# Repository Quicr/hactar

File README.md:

# Device updater

Static GitHub Pages updater written in plain JavaScript, using Web Serial. No
build step, WASM, CDN dependencies, or backend is needed.

## Usage

Open the site in desktop Chrome or Edge, connect the device over USB, select the
chips, and click **Update Device**. Select the device's USB serial port. Close
`ctl`, serial monitors, and other programs using that port first.

Choose a **Firmware version** to select the firmware set under `build/`. The
default is **main**. All chips in an update use the selected folder, and the
selection is locked until the update finishes.

The default update order is **MGMT → UI → NET**. Individual chips can also be
selected. UI and NET updates require MGMT firmware implementing the LINK protocol
from `~/code/link`. The update log is available under **Advanced Options**.

When flashing MGMT, choose **EV16 and older** or **EV17 and newer** (the default).
Every MGMT update applies the selected version: `16` or `17` in the STM32 DATA0
option byte, respectively. The updater preserves the other option bytes, updates
the DATA0 complement, and verifies the result before starting MGMT. If the value
and complement already match, the option-byte read verifies them without an
unnecessary rewrite. The version controls require MGMT to be selected; they
describe the hardware revision, not the firmware release.
Current MGMT firmware only starts when DATA0 is `16` or `17`, so select the
appropriate revision when configuring a chip with an unset board version.

MGMT automatically enters its ROM bootloader using the EV16 DTR/RTS reset
sequence. For boards without automatic reset, set MGMT BOOT0 high, reset the
device, and enable **MGMT is already in bootloader mode** before starting.
After a manual update, release BOOT0 and reset the device to boot normally.

If the browser's serial port rejects DTR/RTS control (`setSignals`), the updater
continues using serial data without automatic MGMT reset. UI and NET updates
still use MGMT's LINK commands to control their boot and reset pins. For MGMT,
enter its bootloader manually if it is not already active; the updater reports
the manual-reset steps if the bootloader does not respond.

Before talking to running MGMT firmware, the updater explicitly releases RTS
(BOOT0) and then DTR (reset), including after reopening the port to change baud
rate. Some serial drivers assert those lines when opening the port.

If MGMT does not answer, open **Advanced Options** for handshake retry details
and the number of serial bytes received. Verify that the selected port is the
device's port and that a manually asserted BOOT0 pin has been released. To
install a replacement `build/main/mgmt/mgmt.bin` on the device, select **MGMT** when
updating; UI/NET-only updates use the MGMT firmware already on the device.

## Firmware files

Publish these files alongside `index.html` for the default `main` firmware set:

| Chip | File | Flash address |
| --- | --- | --- |
| MGMT (STM32F072CB) | `build/main/mgmt/mgmt.bin` | `0x08000000` |
| UI (STM32F405RG) | `build/main/ui/ui.bin` | `0x08000000` |
| NET (ESP32-S3) | `build/main/net/bootloader.bin` | `0x0000` |
| NET | `build/main/net/partition-table.bin` | `0x8000` |
| NET | `build/main/net/net.bin` | `0x10000` |

Additional firmware sets use the same layout in another immediate subfolder,
for example `build/preview/mgmt/mgmt.bin`, `build/preview/ui/ui.bin`, and
`build/preview/net/...`.

The dropdown reads `build/manifest.json`, since GitHub Pages does not provide
directory listings. After adding or removing firmware folders, regenerate and
publish the manifest along with the binaries:

```sh
python3 scripts/generate-firmware-manifest.py
```

The script discovers immediate, non-hidden directories under `build/` and places
`main` first. Include this command in the firmware publishing job when automating
uploads. Missing files in a selected folder stop the update before opening the
serial port; the updater never substitutes binaries from another folder.

NET addresses follow the existing ESP-IDF build's `flasher_args.json`. Its app
must occupy the partition starting at `0x10000`; if the firmware layout changes,
update the addresses in `scripts/flasher.js` together with the binaries.
All selected images download before flashing starts. Only the required STM32
pages/sectors and NET image regions are erased. STM32 images are verified by
reading them back; NET images are checked using the ROM's MD5 command.

## Protocol

- MGMT ROM: 115200 baud, 8E1, STM32 AN3155 bootloader protocol.
- Running MGMT: 1000000 baud, 8E1, `LINK` frames with little-endian type/length.
- UI ROM: 115200 baud, 8E1 on the internal UART, tunneled with `ToUi`/`FromUi`.
- NET ROM: internal UART remains at 1000000 baud, 8N1, SLIP packets tunneled
  with `ToNet`/`FromNet`. Uses the ROM directly without uploading a stub.
- Only Hello, SetPin, SetUiBaudRate, and the two data tunnels are implemented.
  Reset timings and pin identifiers follow `link/src/ctl/{core,flash}.rs`.

The other chip is held in reset during UI/NET flashing and restored afterward.

## Local development

Serve the repository root, for example:

```sh
python3 -m http.server 8000
```

Open `http://localhost:8000`. Web Serial requires HTTPS or localhost; opening
`index.html` directly is not supported. GitHub Pages supplies HTTPS.

Protocol checks use Node's built-in test runner:

```sh
node --experimental-default-type=module --test tests/*.test.js
```

Actual USB flashing must also be checked with a physical device.

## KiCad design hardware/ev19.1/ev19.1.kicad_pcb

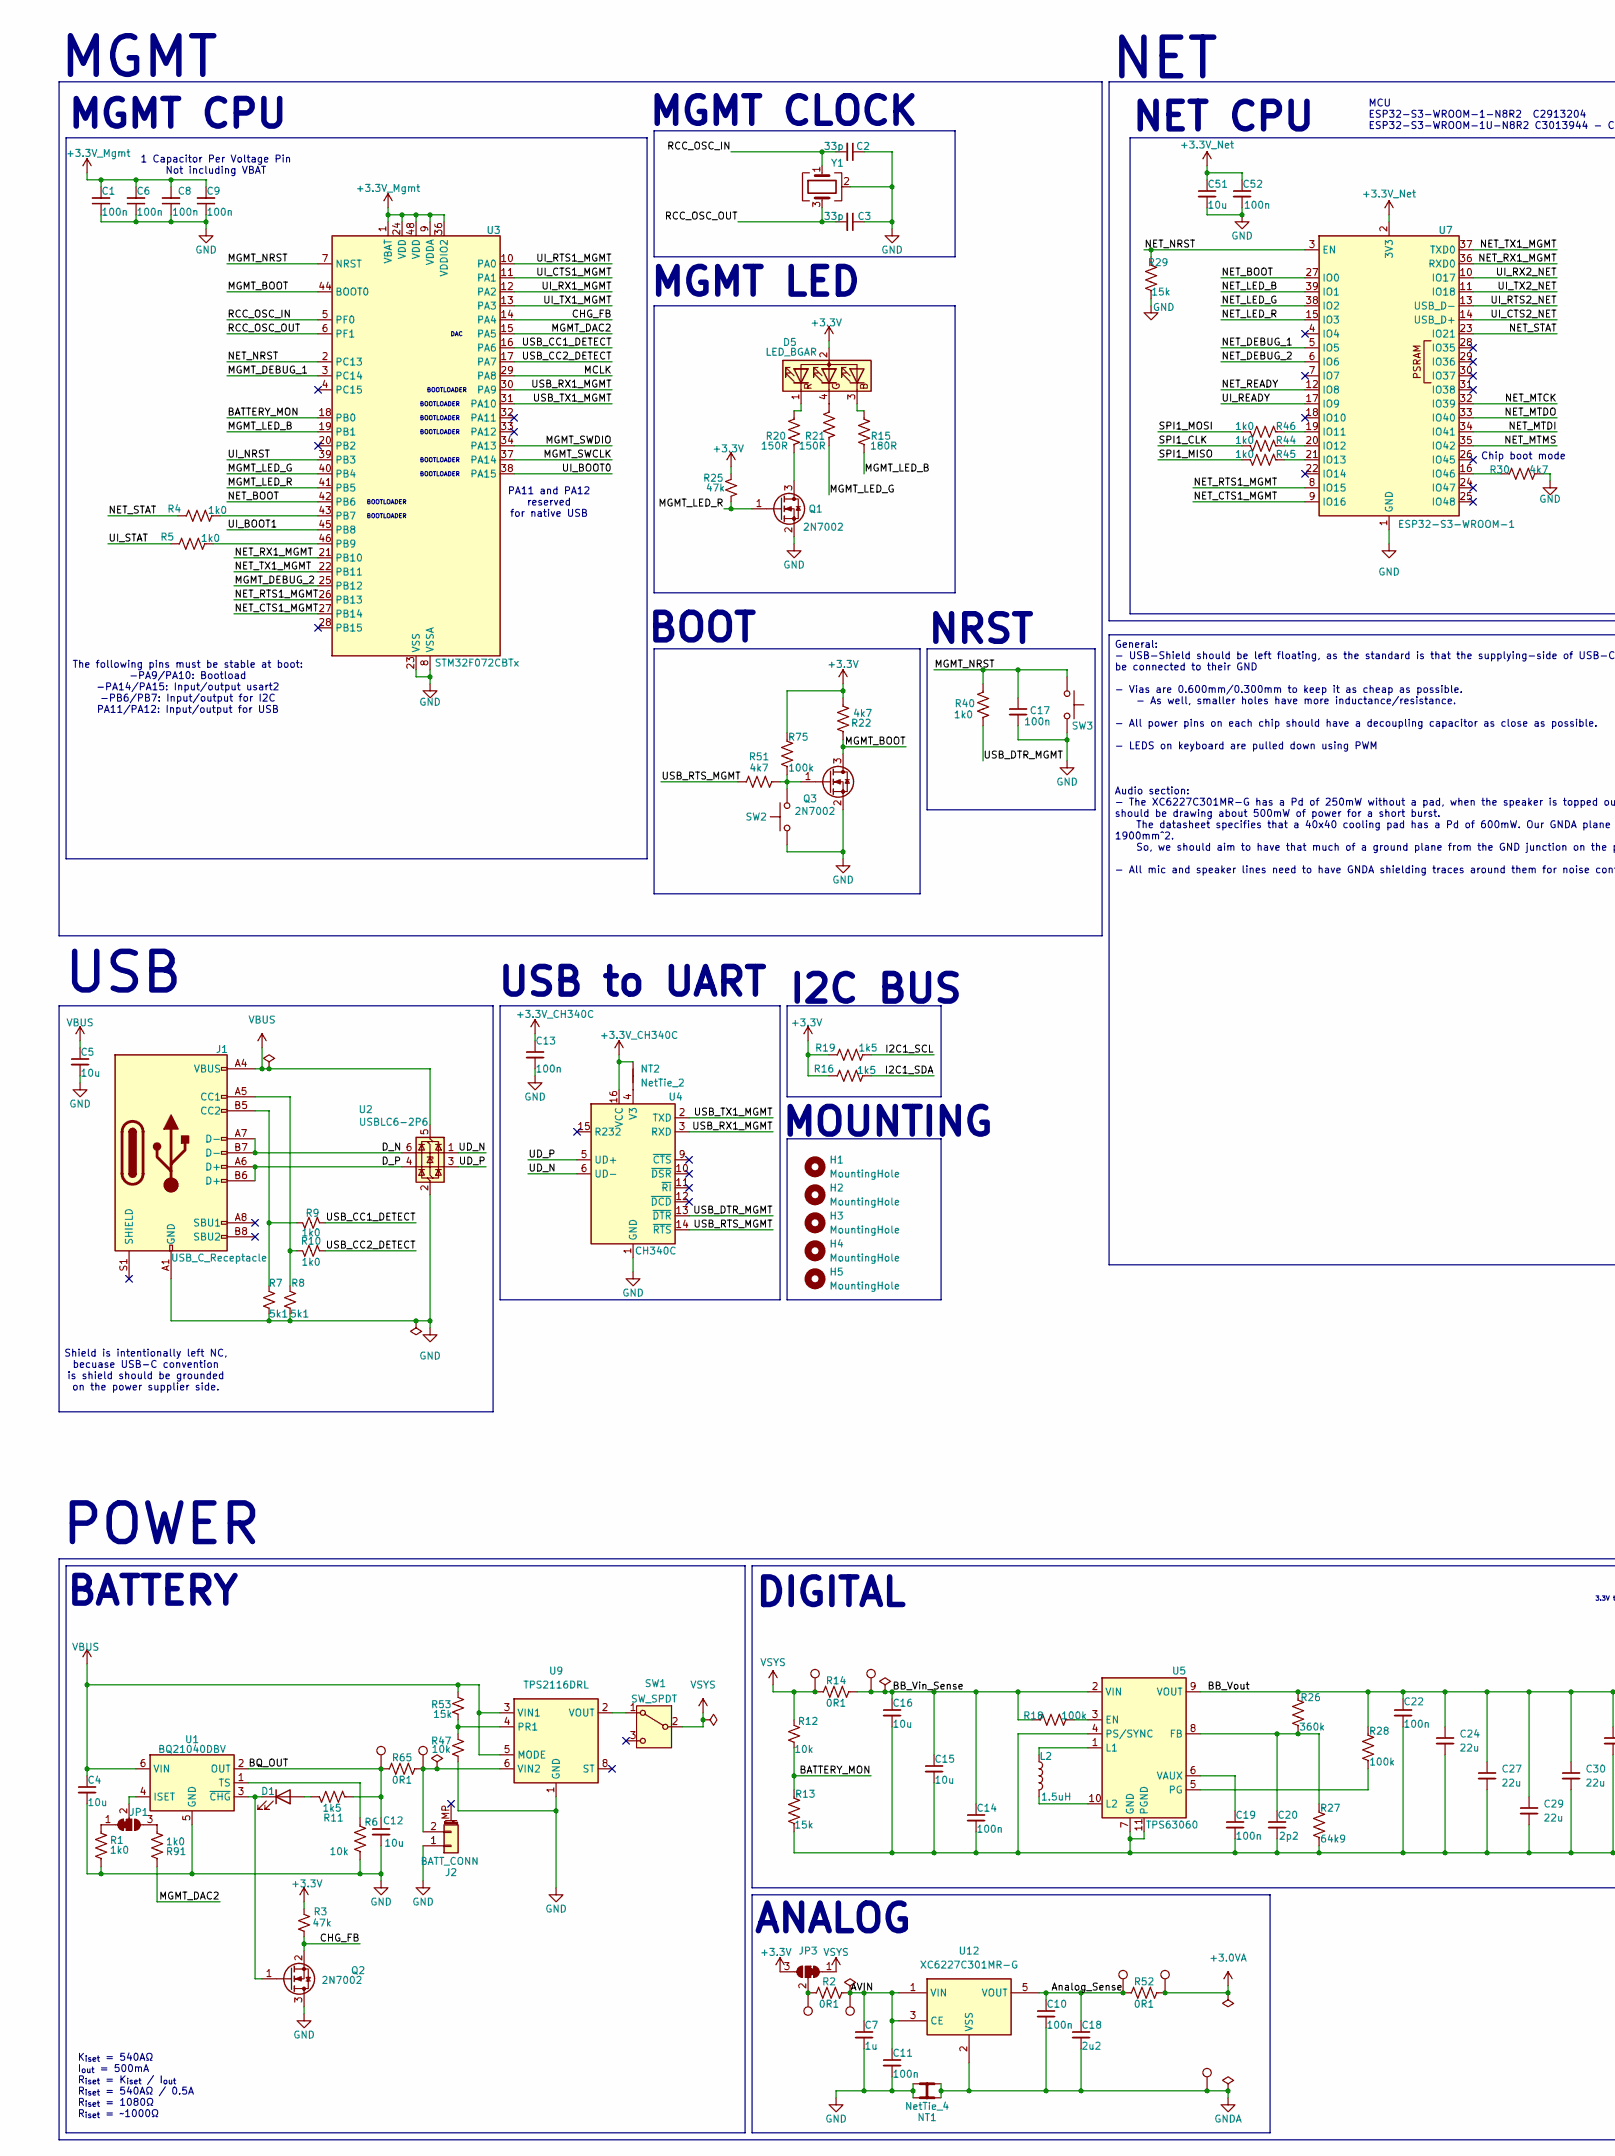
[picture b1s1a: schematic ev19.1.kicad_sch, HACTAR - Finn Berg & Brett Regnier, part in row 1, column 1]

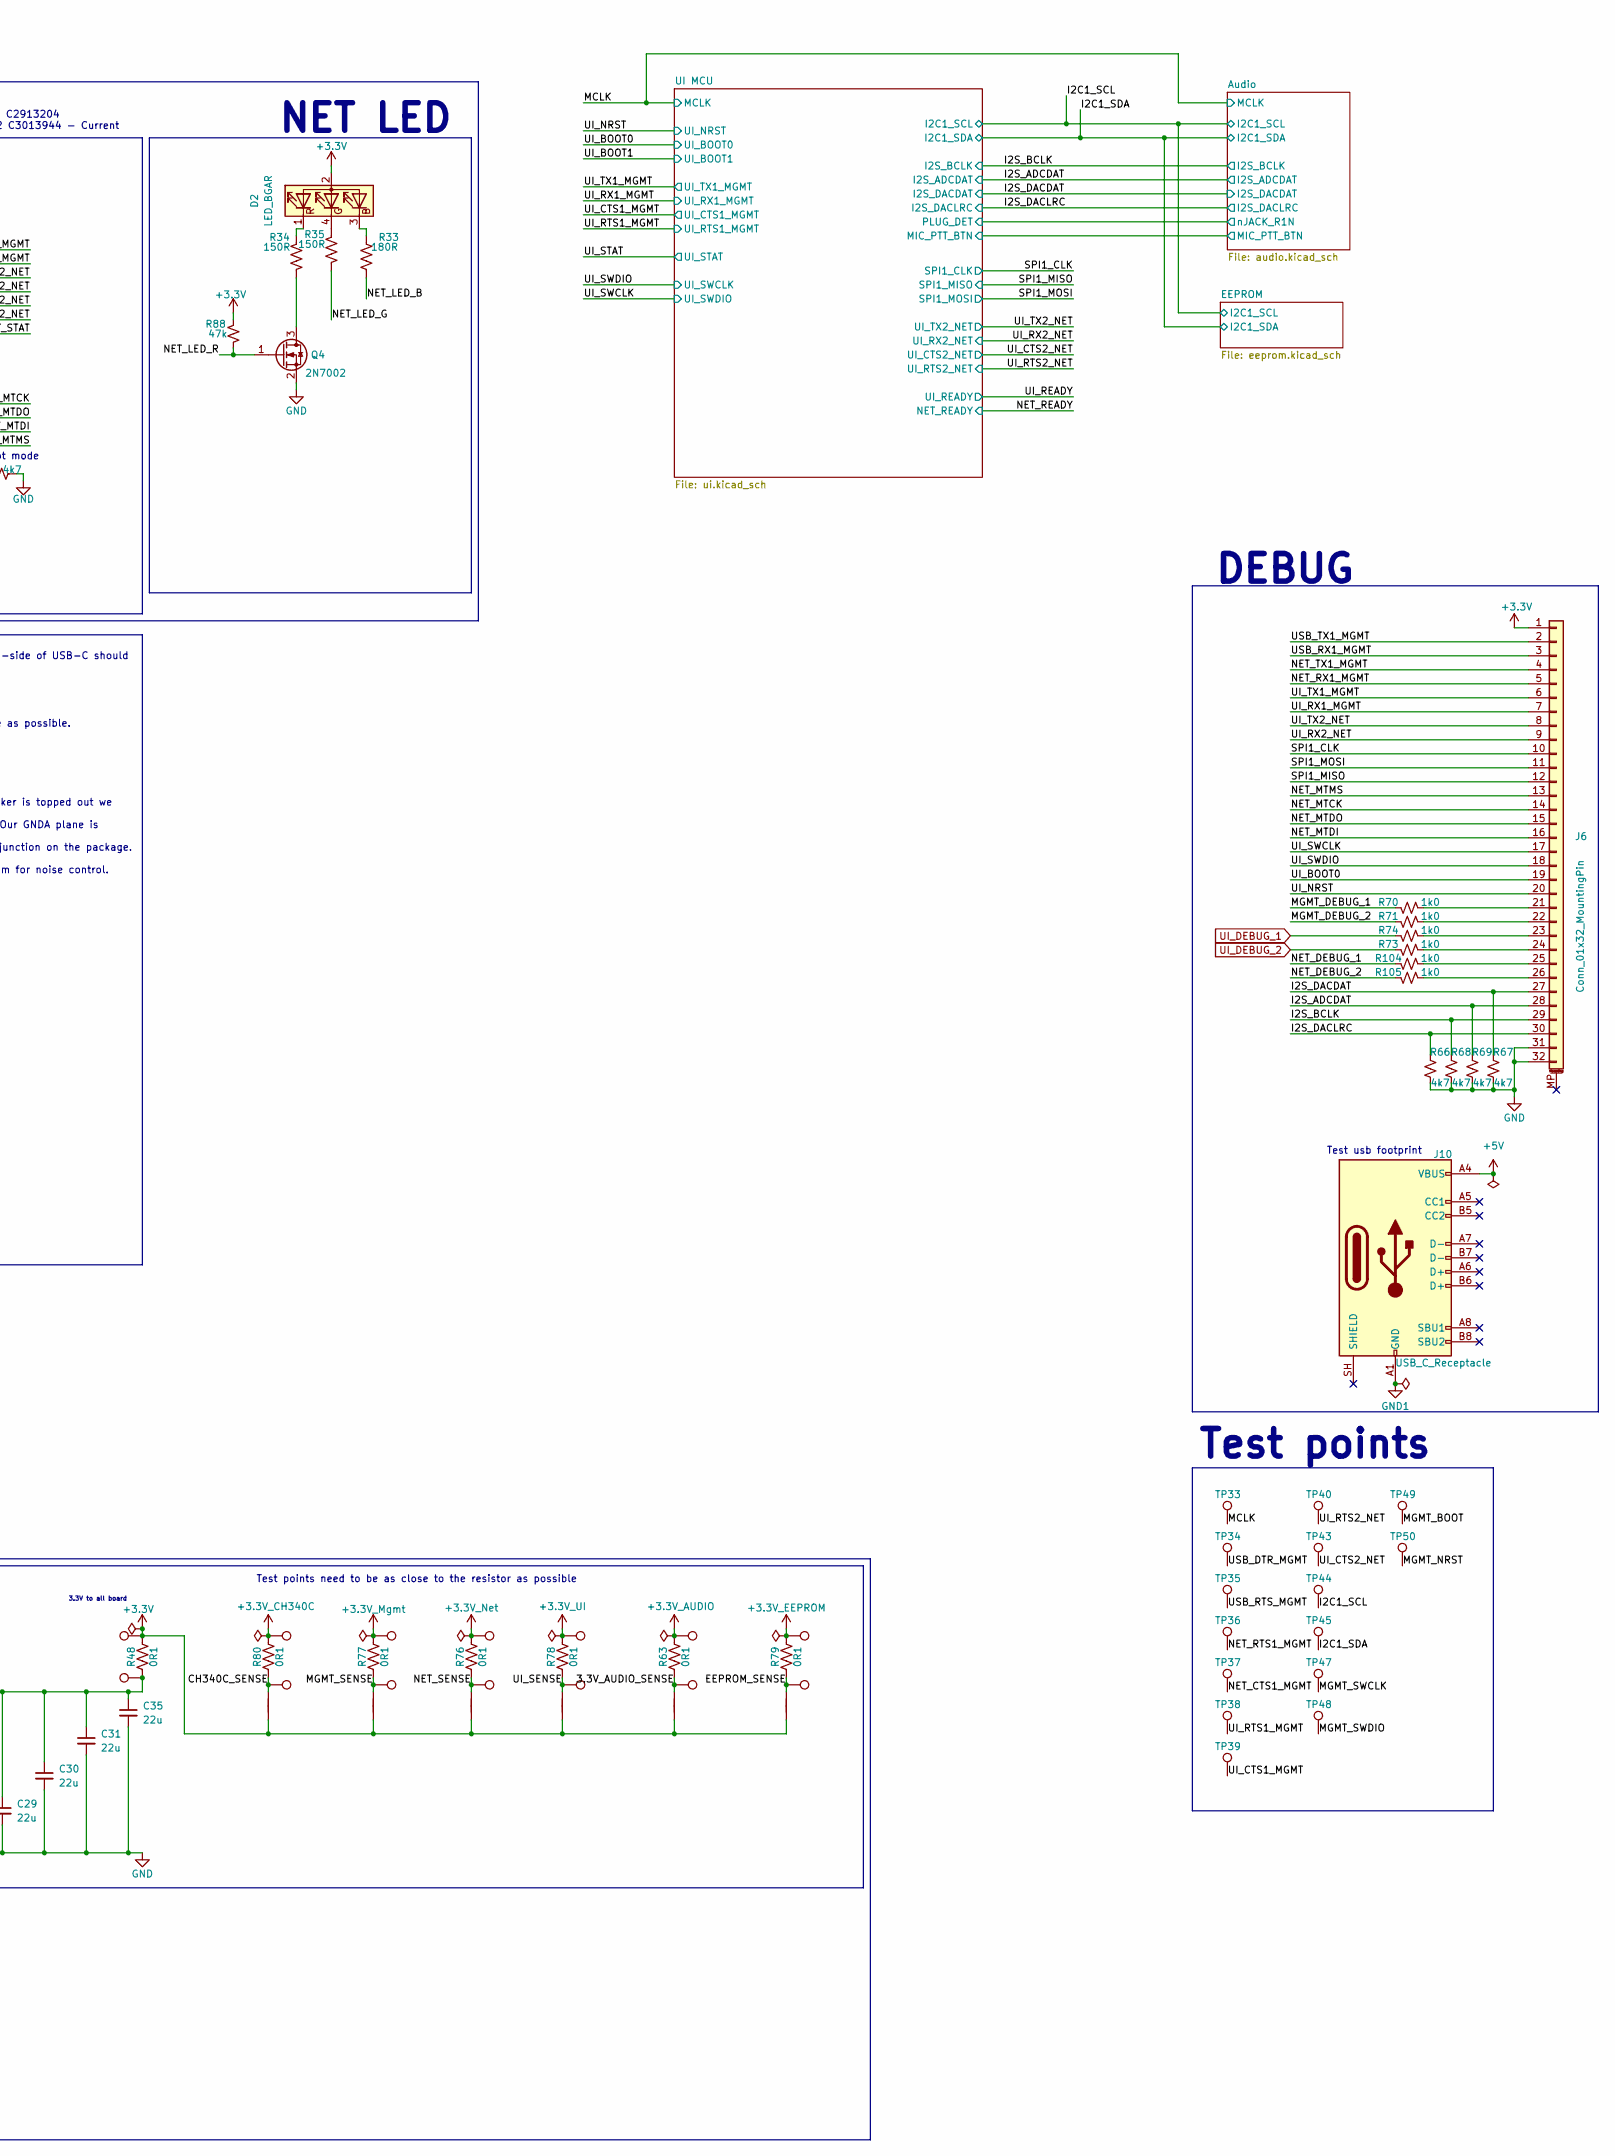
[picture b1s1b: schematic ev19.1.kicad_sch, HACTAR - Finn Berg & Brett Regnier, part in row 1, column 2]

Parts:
C1, C6, C8, C9, C13, C17, C52: 100n; C_0402_1005Metric; JLCPCB Part # C1525
C2, C3: 33p; C_0805_2012Metric; JLCPCB Part # C107115
C4, C5, C12: 10u; C_0402_1005Metric; JLCPCB Part # C307415
C7: 1u; C_0805_2012Metric; JLCPCB Part # C28323
C10, C11, C14, C19, C22: 100n; C_0805_2012Metric; JLCPCB Part # C85866
C15, C16, C51: 10u; C_0805_2012Metric; JLCPCB Part # C87157
C18: 2u2; C_0805_2012Metric; JLCPCB Part # C377773
C20: 2p2; C_0805_2012Metric; JLCPCB Part # C519933
C24, C27, C29, C30, C31, C35: 22u; C_0805_2012Metric; JLCPCB Part # C5674
D1: LED; D_0805_2012Metric; JLCPCB Part # C130114
D2, D5: LED_BGAR; LED-ARRAY-SMD_4P-L1.6-W1.5-TL_NH-B1515RGBA; JLCPCB Part # C2874115
H1, H2, H3, H4: MountingHole; MountingHole_2.7mm_M2.5
H5: MountingHole; Standoff_Hole
J1: USB_C_Receptacle; USB-C_SMD-TYPE-C-31-M-12; JLCPCB Part # C165948
J2: BATT_CONN; JST_PH_S2B-PH-SM4-TB_1x02-1MP_P2.00mm_Horizontal; JLCPCB Part # C295747
J6: Conn_01x32_MountingPin; Hirose_FH12-32S-0.5SH_1x32-1MP_P0.50mm_Horizontal; JLCPCB Part # C597985
J10: USB_C_Receptacle; USB_C_Receptacle_HRO_TYPE-C-31-M-12; JLCPCB Part # C165948
JP1: SolderJumper_3_Bridged12
JP3: SolderJumper_3_Bridged12; SolderJumper-3_P1.3mm_Bridged12_RoundedPad1.0x1.5mm
L2: 1.5uH; L_Coilcraft_XxL4020; JLCPCB Part # C3033018
NT1: NetTie_4; NetTie-4_SMD_Pad0.5mm
NT2, NT5, NT6, NT7, NT8, NT9, NT10: NetTie_2; NetTie-2_SMD_Pad0.5mm
Q1, Q2, Q3, Q4: 2N7002; SOT-23; JLCPCB Part # C8545
R1, R4, R5, R9, R10, R40, R44, R45, R46, R70, R71, R73, R74, R91, R104, R105: 1k0; R_0402_1005Metric; JLCPCB Part # C11702
R2, R14, R48, R52, R63, R65, R76, R77, R78, R79, R80: 0R1; R_1206_3216Metric; JLCPCB Part # C25334
R3, R25, R88: 47k; R_0402_1005Metric; JLCPCB Part # C25792
R6, R12, R47: 10k; R_0402_1005Metric; JLCPCB Part # C25744
R7, R8: 5k1; R_0402_1005Metric; JLCPCB Part # C25905
R11, R16, R19: 1k5; R_0402_1005Metric; JLCPCB Part # C25867
R13, R29, R53: 15k; R_0402_1005Metric; JLCPCB Part # C25756
R15, R33: 180R; R_0402_1005Metric; JLCPCB Part # C25087
R18, R28, R75: 100k; R_0402_1005Metric; JLCPCB Part # C25741
R20, R21, R34, R35: 150R; R_0402_1005Metric; JLCPCB Part # C25082
R22, R30, R51, R66, R67, R68, R69: 4k7; R_0402_1005Metric; JLCPCB Part # C25900
R26: 360k; R_0402_1005Metric; JLCPCB Part # C45956
R27: 64k9; R_0402_1005Metric; JLCPCB Part # C26984
SW1: SW_SPDT; SW-SMD_MK-12C02-G020; JLCPCB Part # C963206
SW2, SW3: SW_Push; KEY-SMD_4P-L4.2-W3.2-P2.20-LS4.6; JLCPCB Part # C139797
TP8: TestPoint; TestPoint_THTPad_D2.0mm_Drill1.0mm
TP11, TP12, TP13, TP14, TP15, TP16, TP17, TP18, TP19, TP20, TP21, TP22, TP23, TP24, TP25, TP26, TP27, TP28, TP29, TP30, TP31, TP32, TP33, TP34, TP35, TP36, TP37, TP38, TP39, TP40, TP43, TP44, TP45, TP47, TP48, TP49, TP50: TestPoint; TestPoint_Pad_D2.0mm
U1: BQ21040DBV; SOT-23-6; JLCPCB Part # C202311
U2: USBLC6-2P6; SOT-666; JLCPCB Part # C2827693
U3: STM32F072CBTx; LQFP-48_7x7mm_P0.5mm; JLCPCB Part # C80488
U4: CH340C; SOIC-16_3.9x9.9mm_P1.27mm; JLCPCB Part # C7464026
U5: TPS63060; Texas_S-PWSON-N10_ThermalVias; JLCPCB Part # C48567
U7: ESP32-S3-WROOM-1; JLCPCB Part # C2913204
U9: TPS2116DRL; SOT-583-8; JLCPCB Part # C3235557
U12: XC6227C301MR-G; SOT-23-5; JLCPCB Part # C484285
Y1: Crystal_GND24; Crystal_SMD_3225-4Pin_3.2x2.5mm; JLCPCB Part # C13738

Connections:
+3.0VA: R52.2, TP28.1 (1_1); also elsewhere on the board
+3.3V: D2.2 (A), D5.2 (A), J6.1, JP3.3 (B), NT5.1, NT6.1, NT7.1, NT8.1, NT9.1, NT10.1, R3.2, R16.1, R19.1, R22.2, R25.2, R48.2, R75.2, R88.2, TP24.1 (1_1); also elsewhere on the board
+3.3V_AUDIO: R63.2, TP13.1 (1_1); also elsewhere on the board
+3.3V_CH340C: C13.1, NT2.2, R80.2, TP21.1 (1_1), U4.16 (VCC)
+3.3V_EEPROM: R79.2, TP12.1 (1_1); also elsewhere on the board
+3.3V_Mgmt: C1.2, C6.2, C8.2, C9.2, R77.2, TP19.1 (1_1), U3.1 (VBAT), U3.9 (VDDA), U3.24 (VDD), U3.36 (VDDIO2), U3.48 (VDD)
+3.3V_Net: C51.1, C52.1, R76.2, TP17.1 (1_1), U7.2 (3V3)
+3.3V_UI: R78.2, TP15.1 (1_1); also elsewhere on the board
/3.3V_AUDIO_SENSE: NT9.2, R63.1, TP14.1 (1_1)
/AVIN: C7.1, C11.1, R2.2, TP30.1 (1_1), U12.1 (VIN), U12.3 (CE)
/Analog_Sense: C10.1, C18.1, R52.1, TP27.1 (1_1), U12.5 (VOUT)
/BATTERY_MON: R12.1, R13.1, U3.18 (PB0)
/BB_Vin_Sense: C14.1, C15.1, C16.1, R14.2, R18.1, TP26.1 (1_1), U5.2 (VIN)
/BB_Vout: C22.1, C24.1, C27.1, C29.1, C30.1, C31.1, C35.1, R26.2, R28.2, R48.1, TP23.1 (1_1), U5.9 (VOUT)
/BQ_OUT: C12.1, R11.1, R65.1, TP31.1 (1_1), U1.2 (OUT)
/CH340C_SENSE: NT5.2, R80.1, TP22.1 (1_1)
/CHG_FB: Q2.2 (S), R3.1, U3.14 (PA4)
/D_N: J1.A7 (D-), J1.B7 (D-), U2.6 (I/O1)
/D_P: J1.A6 (D+), J1.B6 (D+), U2.4 (I/O2)
/EEPROM_SENSE: NT10.2, R79.1, TP11.1 (1_1)
/I2C1_SCL: R19.2, TP44.1 (1_1); also elsewhere on the board
/I2C1_SDA: R16.2, TP45.1 (1_1); also elsewhere on the board
/I2S_ADCDAT: J6.28, R69.1; also elsewhere on the board
/I2S_BCLK: J6.29, R68.1; also elsewhere on the board
/I2S_DACDAT: J6.27, R67.1; also elsewhere on the board
/I2S_DACLRC: J6.30, R66.1; also elsewhere on the board
/MCLK: TP33.1 (1_1), U3.29 (PA8); also elsewhere on the board
/MGMT_BOOT: Q3.3 (D), R22.1, TP49.1 (1_1), U3.44 (BOOT0)
/MGMT_DAC2: R91.1, U3.15 (PA5)
/MGMT_DEBUG_1: R70.1, U3.3 (PC14)
/MGMT_DEBUG_2: R71.1, U3.25 (PB12)
/MGMT_LED_B: R15.2, U3.19 (PB1)
/MGMT_LED_G: R21.2, U3.40 (PB4)
/MGMT_LED_R: Q1.1 (G), R25.1, U3.41 (PB5)
/MGMT_NRST: C17.1, R40.1, SW3.3, SW3.4, TP50.1 (1_1), U3.7 (NRST)
/MGMT_SENSE: NT6.2, R77.1, TP20.1 (1_1)
/MGMT_SWCLK: TP47.1 (1_1), U3.37 (PA14)
/MGMT_SWDIO: TP48.1 (1_1), U3.34 (PA13)
/NET_BOOT: U3.42 (PB6), U7.27 (IO0)
/NET_CTS1_MGMT: TP37.1 (1_1), U3.27 (PB14), U7.9 (IO16)
/NET_DEBUG_1: R104.2, U7.5 (IO5)
/NET_DEBUG_2: R105.2, U7.6 (IO6)
/NET_LED_B: R33.1, U7.39 (IO1)
/NET_LED_G: R35.1, U7.38 (IO2)
/NET_LED_R: Q4.1 (G), R88.1, U7.15 (IO3)
/NET_MTCK: J6.14, U7.32 (IO39)
/NET_MTDI: J6.16, U7.34 (IO41)
/NET_MTDO: J6.15, U7.33 (IO40)
/NET_MTMS: J6.13, U7.35 (IO42)
/NET_NRST: R29.1, U3.2 (PC13), U7.3 (EN)
/NET_READY: U7.12 (IO8); also elsewhere on the board
/NET_RTS1_MGMT: TP36.1 (1_1), U3.26 (PB13), U7.8 (IO15)
/NET_RX1_MGMT: J6.5, U3.21 (PB10), U7.36 (RXD0)
/NET_SENSE: NT7.2, R76.1, TP18.1 (1_1)
/NET_STAT: R4.2, U7.23 (IO21)
/NET_TX1_MGMT: J6.4, U3.22 (PB11), U7.37 (TXD0)
/RCC_OSC_IN: C2.2, U3.5 (PF0), Y1.1
/RCC_OSC_OUT: C3.2, U3.6 (PF1), Y1.3
/SPI1_CLK: J6.10, R44.1; also elsewhere on the board
/SPI1_MISO: J6.12, R45.1; also elsewhere on the board
/SPI1_MOSI: J6.11, R46.1; also elsewhere on the board
/UD_N: U2.1 (I/O1), U4.6 (UD-)
/UD_P: U2.3 (I/O2), U4.5 (UD+)
/UI_BOOT0: J6.19, U3.38 (PA15); also elsewhere on the board
/UI_BOOT1: U3.45 (PB8); also elsewhere on the board
/UI_CTS1_MGMT: TP39.1 (1_1), U3.11 (PA1); also elsewhere on the board
/UI_CTS2_NET: TP43.1 (1_1), U7.14 (USB_D+); also elsewhere on the board
/UI_NRST: J6.20, U3.39 (PB3); also elsewhere on the board
/UI_READY: U7.17 (IO9); also elsewhere on the board
/UI_RTS1_MGMT: TP38.1 (1_1), U3.10 (PA0); also elsewhere on the board
/UI_RTS2_NET: TP40.1 (1_1), U7.13 (USB_D-); also elsewhere on the board
/UI_RX1_MGMT: J6.7, U3.12 (PA2); also elsewhere on the board
/UI_RX2_NET: J6.9, U7.10 (IO17); also elsewhere on the board
/UI_SENSE: NT8.2, R78.1, TP16.1 (1_1)
/UI_STAT: R5.2; also elsewhere on the board
/UI_SWCLK: J6.17; also elsewhere on the board
/UI_SWDIO: J6.18; also elsewhere on the board
/UI_TX1_MGMT: J6.6, U3.13 (PA3); also elsewhere on the board
/UI_TX2_NET: J6.8, U7.11 (IO18); also elsewhere on the board
/USB_CC1_DETECT: R9.1, U3.16 (PA6)
/USB_CC2_DETECT: R10.1, U3.17 (PA7)
/USB_DTR_MGMT: R40.2, TP34.1 (1_1), U4.13 (~DTR)
/USB_RTS_MGMT: R51.1, TP35.1 (1_1), U4.14 (~RTS)
/USB_RX1_MGMT: J6.3, U3.30 (PA9), U4.3 (RXD)
/USB_TX1_MGMT: J6.2, U3.31 (PA10), U4.2 (TXD)
GND: C1.1, C2.1, C3.1, C4.2, C5.2, C6.1, C7.2, C8.1, C9.1, C11.2, C12.2, C13.2, C14.2, C15.2, C16.2, C17.2, C19.2, C20.2, C22.2, C24.2, C27.2, C29.2, C30.2, C31.2, C35.2, C51.2, C52.2, J1.A1 (GND), J1.A12 (GND), J1.B1 (GND), J1.B12 (GND), J2.1, J6.31, J6.32, NT1.1, NT1.3, Q1.2 (S), Q2.3 (D), Q3.2 (S), Q4.2 (S), R1.2, R6.2, R7.1, R8.1, R13.2, R27.1, R29.2, R30.2, R47.1, R66.2, R67.2, R68.2, R69.2, SW2.1, SW2.2, SW3.1, SW3.2, U1.5 (GND), U2.2 (GND), U3.8 (VSSA), U3.23 (VSS), U3.35 (VSS), U3.47 (VSS), U4.1 (GND), U5.4 (PS/SYNC), U5.7 (GND), U5.11 (PGND), U7.1 (GND), U7.40 (GND), U7.41 (GND), U9.1 (GND), Y1.2 (G), Y1.4 (G); also elsewhere on the board
GNDA: C10.2, C18.2, NT1.2, NT1.4, TP8.1 (1_1), U12.2 (VSS); also elsewhere on the board
unnamed: D1.2 (A), R11.2
unnamed: D1.1 (K), Q2.1 (G), U1.3 (~CHG)
unnamed: D2.3 (BK), R33.2
unnamed: D2.4 (GK), R35.2
unnamed: D2.1 (RK), R34.2
unnamed: D5.3 (BK), R15.1
unnamed: D5.4 (GK), R21.1
unnamed: D5.1 (RK), R20.1
unnamed: J1.A5 (CC1), R8.2, R10.2
unnamed: J1.B5 (CC2), R7.2, R9.2
unnamed: J2.2, R65.2, TP32.1 (1_1), U9.6 (VIN2)
unnamed: J6.21, R70.2
unnamed: J6.22, R71.2
unnamed: J6.23, R74.1
unnamed: J6.24, R73.1
unnamed: J6.25, R104.1
unnamed: J6.26, R105.1
unnamed: J10.A1 (GND), J10.A12 (GND), J10.B1 (GND), J10.B12 (GND)
unnamed: J10.A4 (VBUS), J10.A9 (VBUS), J10.B4 (VBUS), J10.B9 (VBUS)
unnamed: JP1.1 (A), R1.1
unnamed: JP1.3 (B), R91.2
unnamed: JP1.2 (C), U1.4 (ISET)
unnamed: JP3.2 (C), R2.1, TP29.1 (1_1)
unnamed: Q1.3 (D), R20.2
unnamed: Q3.1 (G), R51.2, R75.1, SW2.3, SW2.4
unnamed: Q4.3 (D), R34.1
unnamed: SW1.1 (A), U9.2 (VOUT), U9.7 (VOUT)
unnamed: R6.1, U1.1 (TS)
unnamed: R4.1, U3.43 (PB7)
unnamed: R5.1, U3.46 (PB9)
unnamed: NT2.1, U4.4 (V3)
unnamed: R18.2, U5.3 (EN)
unnamed: C20.1, R26.1, R27.2, U5.8 (FB)
unnamed: L2.1, U5.1 (L1)
unnamed: L2.2, U5.10 (L2)
unnamed: R28.1, U5.5 (PG)
unnamed: C19.1, U5.6 (VAUX)
unnamed: R46.2, U7.19 (IO11)
unnamed: R44.2, U7.20 (IO12)
unnamed: R45.2, U7.21 (IO13)
unnamed: R30.1, U7.16 (IO46)
unnamed: R47.2, R53.1, U9.4 (PR1)
UI_DEBUG_1: R74.2; also elsewhere on the board
UI_DEBUG_2: R73.2; also elsewhere on the board
VBUS: C4.1, C5.1, J1.A4 (VBUS), J1.A9 (VBUS), J1.B4 (VBUS), J1.B9 (VBUS), R53.2, U1.6 (VIN), U2.5 (VBUS), U9.3 (VIN1), U9.5 (MODE)
VSYS: JP3.1 (A), R12.2, R14.1, SW1.2 (B), TP25.1 (1_1)

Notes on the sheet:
MGMT
BOOTLOADER
USB to UART
DAC
NET CPU
MGMT CLOCK
MGMT CPU
Test points need to be as close to the resistor as possible
NET
Test points
POWER
K_{iset} = 540AΩ I_{out} = 500mA R_{iset} = K_{iset} / I_{out} R_{iset} = 540AΩ / 0.5A R_{iset} = 1080Ω R_{iset} = ~1000Ω
MOUNTING
BATTERY
NET LED
Chip boot mode
NRST
The following pins must be stable at boot: -PA9/PA10: Bootload -PA14/PA15: Input/output usart2 -PB6/PB7: Input/output for I2C PA11/PA12: Input/output for USB
DIGITAL
Test usb footprint
Shield is intentionally left NC, becuase USB-C convention is shield should be grounded on the power supplier side.
MCU ESP32-S3-WROOM-1-N8R2 C2913204 ESP32-S3-WROOM-1U-N8R2 C3013944 - Current
BOOT
PA11 and PA12 reserved for native USB
I2C BUS
USB
MGMT LED
3.3V to all board
DEBUG
1 Capacitor Per Voltage Pin Not including VBAT
ANALOG
General: - USB-Shield should be left floating, as the standard is that the supplying-side of USB-C should be connected to their GND - Vias are 0.600mm/0.300mm to keep it as cheap as possible. - As well, smaller holes have more inductance/resistance. - All power pins on each chip should have a decou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

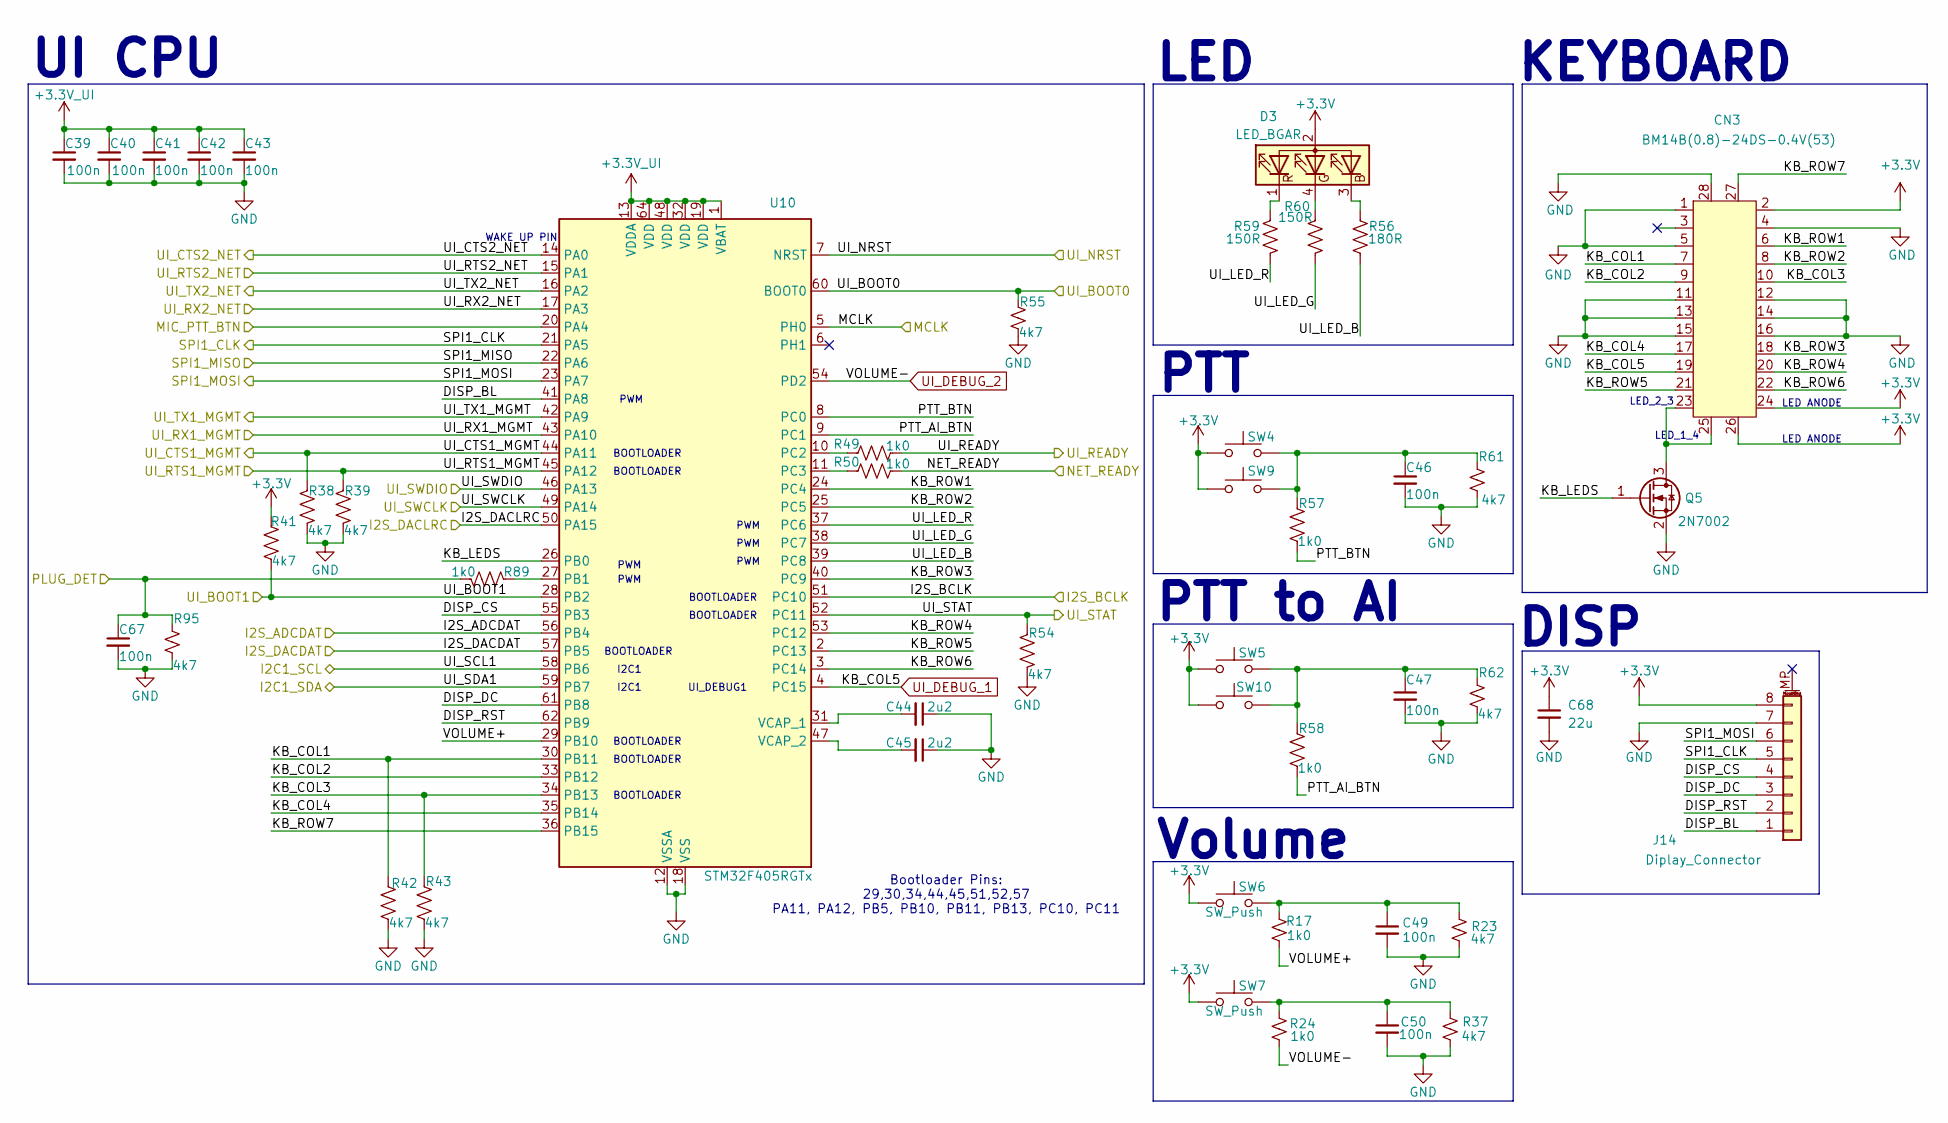
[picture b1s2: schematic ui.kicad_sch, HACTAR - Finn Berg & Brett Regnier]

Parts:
C39, C40, C41, C42, C43, C46, C47, C49, C50, C67: 100n; C_0402_1005Metric; JLCPCB Part # C1525
C44, C45: 2u2; C_0402_1005Metric; JLCPCB Part # C12530
C68: 22u; C_0805_2012Metric; JLCPCB Part # C5674
CN3: BM14B(0.8)-24DS-0.4V(53); BM14B(0.B)-24DS-0.4V(53); JLCPCB Part # C3640874
D3: LED_BGAR; LED-ARRAY-SMD_4P-L1.6-W1.5-TL_NH-B1515RGBA; JLCPCB Part # C2874115
J14: Diplay_Connector; JST_PH_S8B-PH-SM4-TB_1x08-1MP_P2.00mm_Horizontal; JLCPCB Part # C265121
Q5: 2N7002; SOT-23; JLCPCB Part # C8545
R17, R24, R49, R50, R57, R58, R89: 1k0; R_0402_1005Metric; JLCPCB Part # C11702
R23, R37, R38, R39, R41, R42, R43, R54, R55, R61, R62, R95: 4k7; R_0402_1005Metric; JLCPCB Part # C25900
R56: 180R; R_0402_1005Metric; JLCPCB Part # C25087
R59, R60: 150R; R_0402_1005Metric; JLCPCB Part # C25082
SW4, SW5, SW6, SW7: SW_Push; SW-SMD_SHOU_TS36CA-0.6; JLCPCB Part # C2906288
SW9, SW10: SW_Push; SW-SMD_4P-L5.1-W5.1-P3.70-LS6.5-TL_H1.5; JLCPCB Part # C318886
U10: STM32F405RGTx; LQFP-64_10x10mm_P0.5mm; JLCPCB Part # C15742

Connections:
+3.3V: C68.1, CN3.2, CN3.24, CN3.26, D3.2 (A), J14.8, R41.1, SW4.1, SW5.1, SW6.1, SW7.1, SW9.1, SW9.2, SW10.1, SW10.2; also elsewhere on the board
+3.3V_UI: C39.1, C40.1, C41.1, C42.1, C43.1, U10.1 (VBAT), U10.13 (VDDA), U10.19 (VDD), U10.32 (VDD), U10.48 (VDD), U10.64 (VDD); also elsewhere on the board
/Audio/MIC_PTT_BTN: U10.20 (PA4); also elsewhere on the board
/Audio/nJACK_R1N: C67.1, R89.1, R95.2; also elsewhere on the board
/I2C1_SCL: U10.58 (PB6); also elsewhere on the board
/I2C1_SDA: U10.59 (PB7); also elsewhere on the board
/I2S_ADCDAT: U10.56 (PB4); also elsewhere on the board
/I2S_BCLK: U10.51 (PC10); also elsewhere on the board
/I2S_DACDAT: U10.57 (PB5); also elsewhere on the board
/I2S_DACLRC: U10.50 (PA15); also elsewhere on the board
/MCLK: U10.5 (PH0); also elsewhere on the board
/NET_READY: R50.1; also elsewhere on the board
/SPI1_CLK: J14.5, U10.21 (PA5); also elsewhere on the board
/SPI1_MISO: U10.22 (PA6); also elsewhere on the board
/SPI1_MOSI: J14.6, U10.23 (PA7); also elsewhere on the board
/UI MCU/DISP_BL: J14.1, U10.41 (PA8)
/UI MCU/DISP_CS: J14.4, U10.55 (PB3)
/UI MCU/DISP_DC: J14.3, U10.61 (PB8)
/UI MCU/DISP_RST: J14.2, U10.62 (PB9)
/UI MCU/KB_COL1: CN3.7, R42.2, U10.30 (PB11)
/UI MCU/KB_COL2: CN3.9, U10.33 (PB12)
/UI MCU/KB_COL3: CN3.10, R43.2, U10.34 (PB13)
/UI MCU/KB_COL4: CN3.17, U10.35 (PB14)
/UI MCU/KB_LEDS: Q5.1 (G), U10.26 (PB0)
/UI MCU/KB_ROW1: CN3.6, U10.24 (PC4)
/UI MCU/KB_ROW2: CN3.8, U10.25 (PC5)
/UI MCU/KB_ROW3: CN3.18, U10.40 (PC9)
/UI MCU/KB_ROW4: CN3.20, U10.53 (PC12)
/UI MCU/KB_ROW5: CN3.21, U10.2 (PC13)
/UI MCU/KB_ROW6: CN3.22, U10.3 (PC14)
/UI MCU/KB_ROW7: CN3.27, U10.36 (PB15)
/UI MCU/PTT_AI_BTN: R58.1, U10.9 (PC1)
/UI MCU/PTT_BTN: R57.1, U10.8 (PC0)
/UI MCU/UI_LED_B: R56.1, U10.39 (PC8)
/UI MCU/UI_LED_G: R60.1, U10.38 (PC7)
/UI MCU/UI_LED_R: R59.1, U10.37 (PC6)
/UI MCU/VOLUME+: R17.1, U10.29 (PB10)
/UI_BOOT0: R55.1, U10.60 (BOOT0); also elsewhere on the board
/UI_BOOT1: R41.2, U10.28 (PB2); also elsewhere on the board
/UI_CTS1_MGMT: R38.2, U10.44 (PA11); also elsewhere on the board
/UI_CTS2_NET: U10.14 (PA0); also elsewhere on the board
/UI_NRST: U10.7 (NRST); also elsewhere on the board
/UI_READY: R49.1; also elsewhere on the board
/UI_RTS1_MGMT: R39.2, U10.45 (PA12); also elsewhere on the board
/UI_RTS2_NET: U10.15 (PA1); also elsewhere on the board
/UI_RX1_MGMT: U10.43 (PA10); also elsewhere on the board
/UI_RX2_NET: U10.17 (PA3); also elsewhere on the board
/UI_STAT: R54.2, U10.52 (PC11); also elsewhere on the board
/UI_SWCLK: U10.46 (PA13); also elsewhere on the board
/UI_SWDIO: U10.49 (PA14); also elsewhere on the board
/UI_TX1_MGMT: U10.42 (PA9); also elsewhere on the board
/UI_TX2_NET: U10.16 (PA2); also elsewhere on the board
GND: C39.2, C40.2, C41.2, C42.2, C43.2, C44.1, C45.1, C46.2, C47.2, C49.2, C50.2, C67.2, C68.2, CN3.1, CN3.4, CN3.5, CN3.11, CN3.12, CN3.13, CN3.14, CN3.15, CN3.16, CN3.28, J14.7, Q5.2 (S), R23.1, R37.1, R38.1, R39.1, R42.1, R43.1, R54.1, R55.2, R61.1, R62.1, R95.1, U10.12 (VSSA), U10.18 (VSS), U10.63 (VSS); also elsewhere on the board
unnamed: C46.1, R57.2, R61.2, SW4.2, SW9.3, SW9.4
unnamed: C47.1, R58.2, R62.2, SW5.2, SW10.3, SW10.4
unnamed: C49.1, R17.2, R23.2, SW6.2
unnamed: C50.1, R24.2, R37.2, SW7.2
unnamed: D3.3 (BK), R56.2
unnamed: D3.4 (GK), R60.2
unnamed: D3.1 (RK), R59.2
unnamed: CN3.23, CN3.25, Q5.3 (D)
unnamed: R89.2, U10.27 (PB1)
unnamed: R49.2, U10.10 (PC2)
unnamed: R50.2, U10.11 (PC3)
unnamed: C44.2, U10.31 (VCAP_1)
unnamed: C45.2, U10.47 (VCAP_2)
UI_DEBUG_1: CN3.19, U10.4 (PC15); also elsewhere on the board
UI_DEBUG_2: R24.1, U10.54 (PD2); also elsewhere on the board

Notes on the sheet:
BOOTLOADER
Volume
I2C1
LED_1_4
KEYBOARD
LED ANODE
UI CPU
PTT to AI
DISP
PTT
Bootloader Pins: 29,30,34,44,45,51,52,57 PA11, PA12, PB5, PB10, PB11, PB13, PC10, PC11
PWM
LED_2_3
LED
WAKE UP PIN
UI_DEBUG1
